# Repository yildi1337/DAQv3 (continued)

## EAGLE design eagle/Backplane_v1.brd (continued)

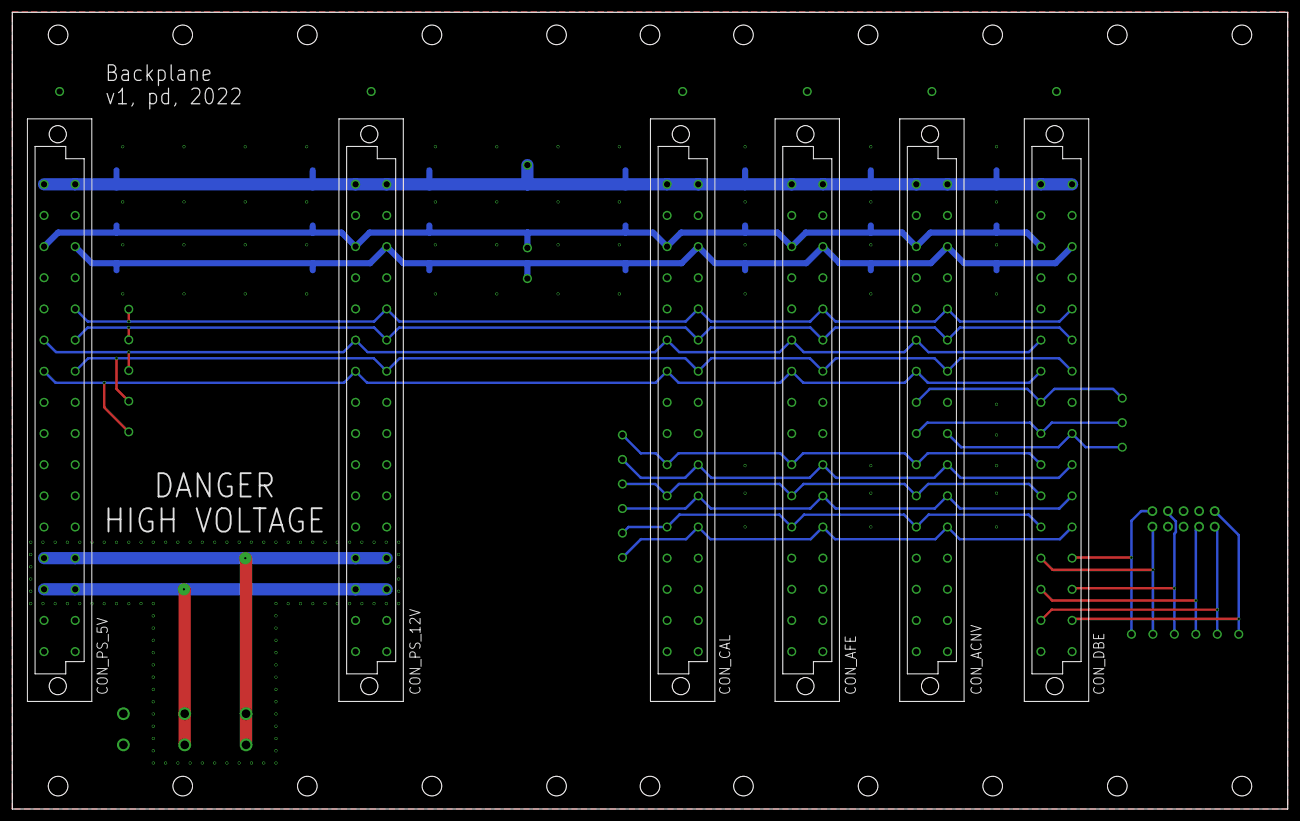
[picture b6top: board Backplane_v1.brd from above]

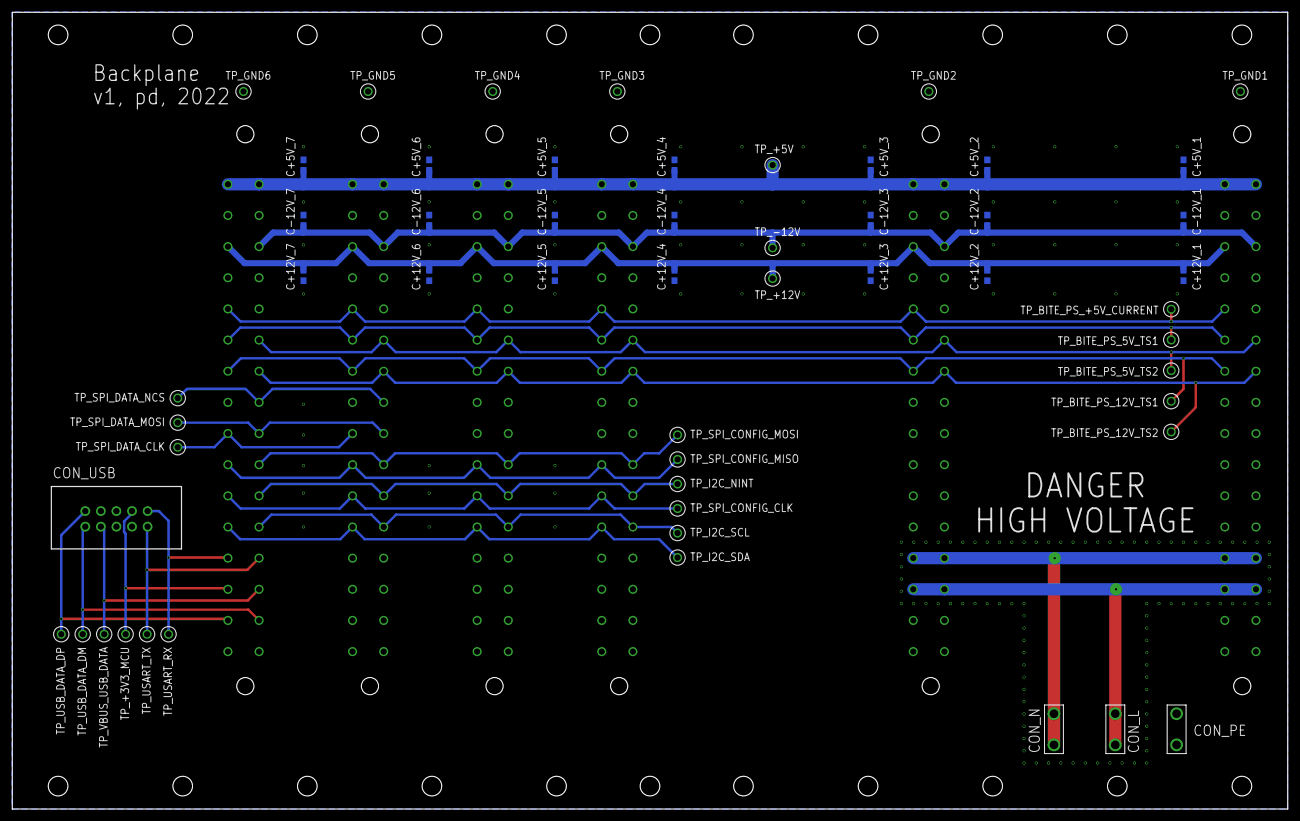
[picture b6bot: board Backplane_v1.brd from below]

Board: 2 copper layers, 208.0 x 129.9 mm, 60 parts (54 on the bottom side), 26 nets.

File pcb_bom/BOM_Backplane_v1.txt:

Stückliste exportiert aus D:/OneDrive/Elektronikprojekte/DAQ v3 STM32H7/Eagle/Backplane v1/Backplane_v1.sch am 20.03.2022 14:57

Qty Value          Device                          Package                         Parts                                                                                                                                                                                                                                                                                                                                                                                                                             Description                POPULARITY SPICEPREFIX
29                 RSPRO-1MM-TERMINAL-POST-2622034 RSPRO-1MM-TERMINAL-POST-2622034 TP_+3V3_MCU, TP_+5V, TP_+12V, TP_-12V, TP_BITE_PS_+5V_CURRENT, TP_BITE_PS_5V_TS1, TP_BITE_PS_5V_TS2, TP_BITE_PS_12V_TS1, TP_BITE_PS_12V_TS2, TP_GND1, TP_GND2, TP_GND3, TP_GND4, TP_GND5, TP_GND6, TP_I2C_NINT, TP_I2C_SCL, TP_I2C_SDA, TP_SPI_CONFIG_CLK, TP_SPI_CONFIG_MISO, TP_SPI_CONFIG_MOSI, TP_SPI_DATA_CLK, TP_SPI_DATA_MOSI, TP_SPI_DATA_NCS, TP_USART_RX, TP_USART_TX, TP_USB_DATA_DM, TP_USB_DATA_DP, TP_VBUS_USB_DATA                                                  
6   09032326825    09032326825                     09032326825                     CON_ACNV, CON_AFE, CON_CAL, CON_DBE, CON_PS_5V, CON_PS_12V                                                                                                                                                                                                                                                                                                                                                                                                                         
21  100n           C-EUC0603                       C0603                           C+5V_1, C+5V_2, C+5V_3, C+5V_4, C+5V_5, C+5V_6, C+5V_7, C+12V_1, C+12V_2, C+12V_3, C+12V_4, C+12V_5, C+12V_6, C+12V_7, C-12V_1, C-12V_2, C-12V_3, C-12V_4, C-12V_5, C-12V_6, C-12V_7                                                                                                                                                                                                                                              CAPACITOR, European symbol 73         C          
3   63824-1        63824-1                         63824-1                         CON_L, CON_N, CON_PE                                                                                                                                                                                                                                                                                                                                                                                                                                                               
1   TST-105-01-T-D TST-105-01-T-D                  TST-105-01-T-D                  CON_USB

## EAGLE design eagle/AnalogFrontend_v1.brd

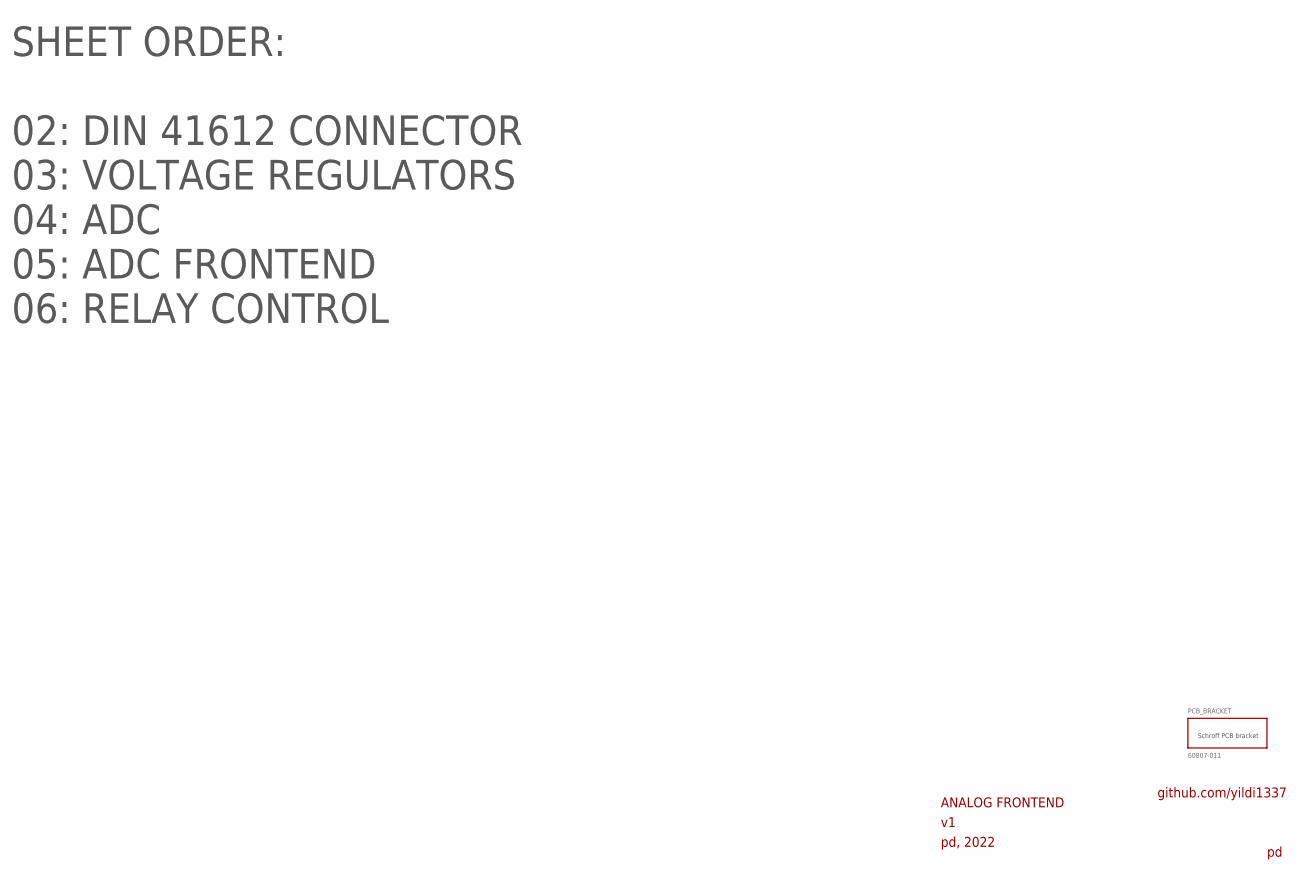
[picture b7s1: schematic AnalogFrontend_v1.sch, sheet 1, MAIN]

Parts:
PCB_BRACKET: 60807-011

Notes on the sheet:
ANALOG FRONTEND
pd, 2022
github.com/yildi1337
SHEET ORDER: 02: DIN 41612 CONNECTOR 03: VOLTAGE REGULATORS 04: ADC 05: ADC FRONTEND 06: RELAY CONTROL

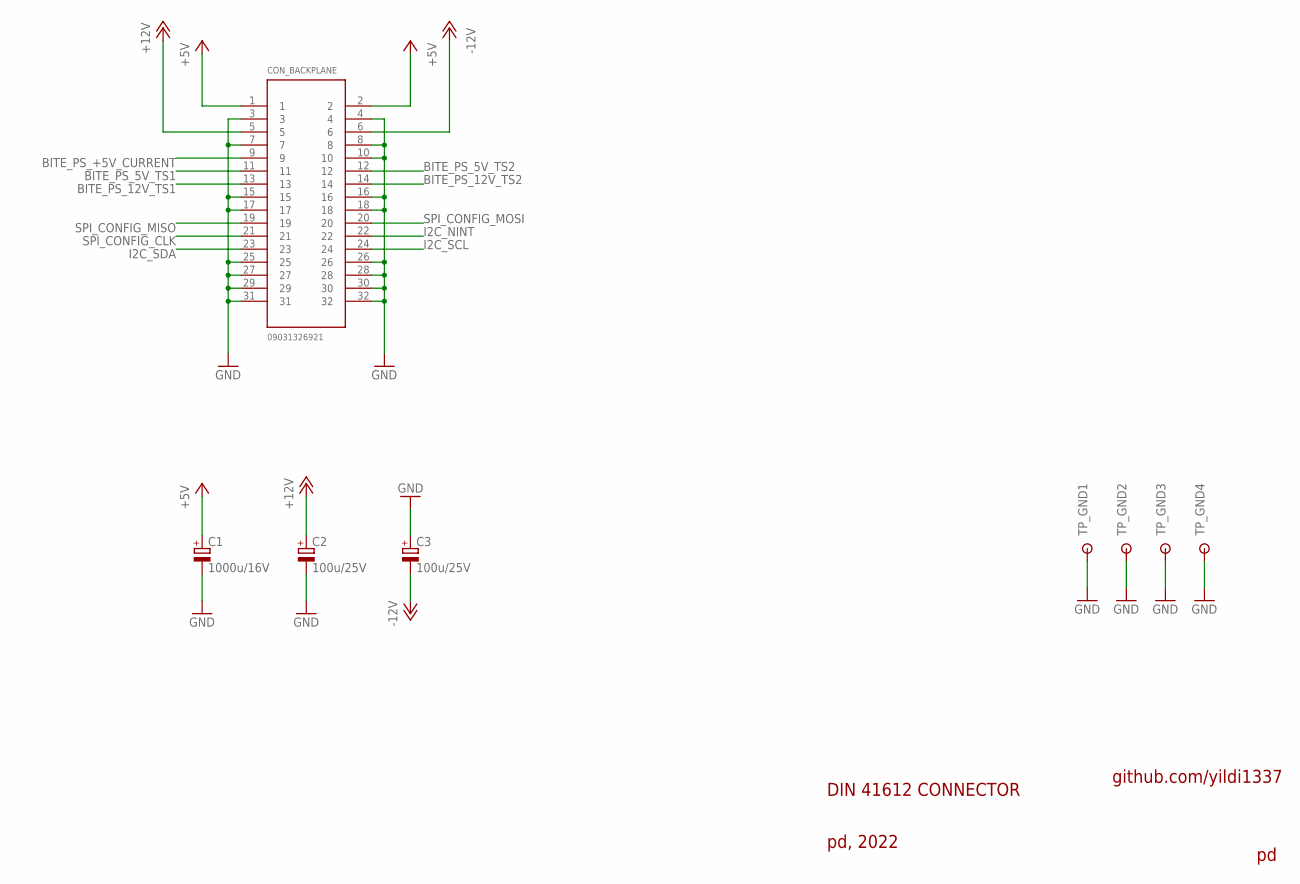
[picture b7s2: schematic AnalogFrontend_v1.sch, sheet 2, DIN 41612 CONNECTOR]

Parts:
C1: 1000u/16V; 153CLV-1010
C2, C3: 100u/25V; 153CLV-0810
CON_BACKPLANE: 09031326921
TP_GND1, TP_GND2, TP_GND3, TP_GND4: RSPRO-1MM-TERMINAL-POST-2622034

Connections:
+5V: C1.+, CON_BACKPLANE.1, CON_BACKPLANE.2; also elsewhere on the board
+12V: C2.+, CON_BACKPLANE.5; also elsewhere on the board
-12V: C3.-, CON_BACKPLANE.6; also elsewhere on the board
BITE_PS_5V_TS1: CON_BACKPLANE.11
BITE_PS_5V_TS2: CON_BACKPLANE.12
BITE_PS_12V_TS1: CON_BACKPLANE.13
BITE_PS_12V_TS2: CON_BACKPLANE.14
BITE_PS_+5V_CURRENT: CON_BACKPLANE.9
GND: C1.-, C2.-, C3.+, CON_BACKPLANE.3, CON_BACKPLANE.4, CON_BACKPLANE.7, CON_BACKPLANE.8, CON_BACKPLANE.10, CON_BACKPLANE.15, CON_BACKPLANE.16, CON_BACKPLANE.17, CON_BACKPLANE.18, CON_BACKPLANE.25, CON_BACKPLANE.26, CON_BACKPLANE.27, CON_BACKPLANE.28, CON_BACKPLANE.29, CON_BACKPLANE.30, CON_BACKPLANE.31, CON_BACKPLANE.32, TP_GND1.P$1, TP_GND2.P$1, TP_GND3.P$1, TP_GND4.P$1; also elsewhere on the board
I2C_NINT: CON_BACKPLANE.22; also elsewhere on the board
I2C_SCL: CON_BACKPLANE.24; also elsewhere on the board
I2C_SDA: CON_BACKPLANE.23; also elsewhere on the board
SPI_CONFIG_CLK: CON_BACKPLANE.21; also elsewhere on the board
SPI_CONFIG_MISO: CON_BACKPLANE.19; also elsewhere on the board
SPI_CONFIG_MOSI: CON_BACKPLANE.20; also elsewhere on the board

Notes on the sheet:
DIN 41612 CONNECTOR
pd, 2022
github.com/yildi1337

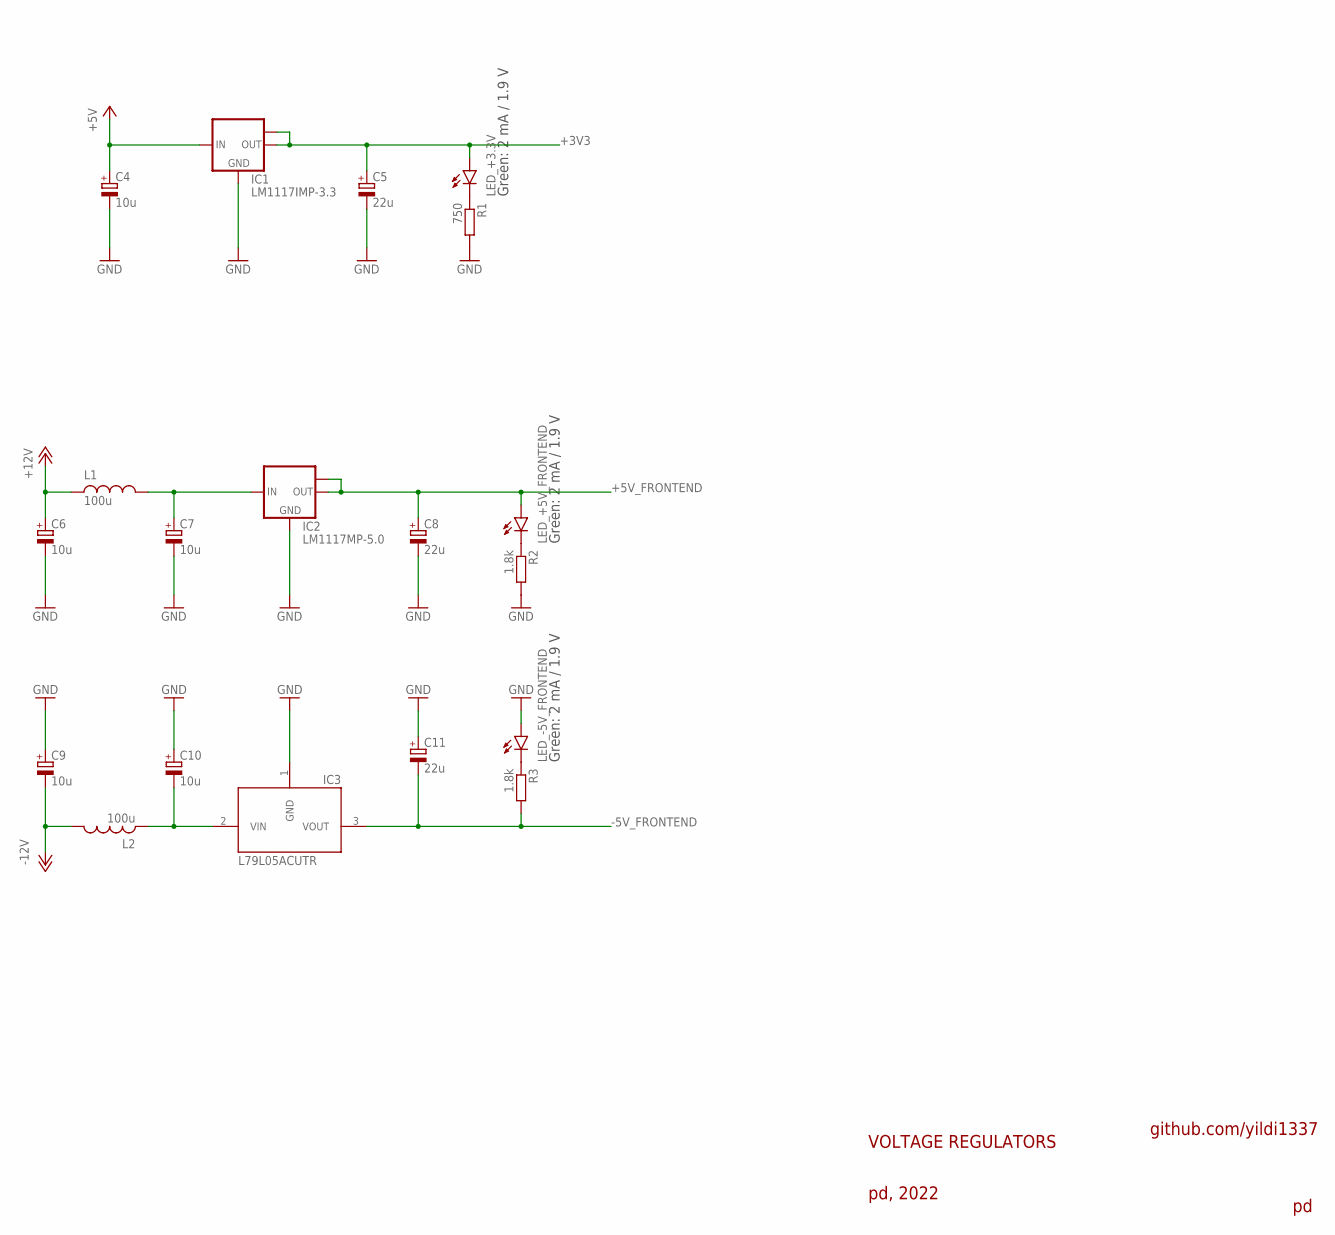
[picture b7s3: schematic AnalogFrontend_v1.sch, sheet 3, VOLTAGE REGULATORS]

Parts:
C4, C6, C7, C9, C10: 10u; CT3216
C5, C8, C11: 22u; CT6032
IC1: LM1117IMP-3.3; SOT223
IC2: LM1117MP-5.0; SOT223
IC3: L79L05ACUTR
L1, L2: 100u; VLS6045AF-101M
LED_+3.3V, LED_+5V_FRONTEND: LEDCHIP-LED0603; CHIP-LED0603
LED_-5V_FRONTEND: LEDCHIP-LED0603; CHIP-LED0603
R1: 750; R0603
R2, R3: 1.8k; R0603

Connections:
+3V3: C5.+, IC1.2 (OUT), IC1.TAB (OUT1), LED_+3.3V.A; also elsewhere on the board
+5V: C4.+, IC1.3 (IN); also elsewhere on the board
+5V_FRONTEND: C8.+, IC2.2 (OUT), IC2.TAB (OUT1), LED_+5V_FRONTEND.A; also elsewhere on the board
+12V: C6.+, L1.1; also elsewhere on the board
-5V_FRONTEND: C11.-, IC3.3 (VOUT), R3.2; also elsewhere on the board
-12V: C9.-, L2.2; also elsewhere on the board
GND: C4.-, C5.-, C6.-, C7.-, C8.-, C9.+, C10.+, C11.+, IC1.1 (GND), IC2.1 (GND), IC3.1 (GND), LED_-5V_FRONTEND.A, R1.2, R2.2; also elsewhere on the board
unnamed: LED_+5V_FRONTEND.C, R2.1
unnamed: C7.+, IC2.3 (IN), L1.2
unnamed: C10.-, IC3.2 (VIN), L2.1
unnamed: LED_-5V_FRONTEND.C, R3.1
unnamed: LED_+3.3V.C, R1.1

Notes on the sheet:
VOLTAGE REGULATORS
pd, 2022
github.com/yildi1337
Green: 2 mA / 1.9 V

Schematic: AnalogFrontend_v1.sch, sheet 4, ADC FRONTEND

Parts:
C57, C58, C634545, C644545: 100n; C0603
C61, C62: 1n; C0603
CON_INT_CH1, CON_INT_CH2: 2337019-1
CON_IN_CH1, CON_IN_CH2: DELOCK_65848
CON_OUT_CH1, CON_OUT_CH2: DELOCK_65848
IC9: OP27GSZ; SO08
LED_SHORT_CH1, LED_SHORT_CH2: 113-305-04
OP1, OP2: LT1028CS8
R33, R34: 1M; R0603
R3164654, R3245454: 150; R0603
RELAY1, RELAY2: 5-1462037-8
TP_FDA1_IN, TP_FDA2_IN: RSPRO-1MM-TERMINAL-POST-2622034

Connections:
+5V: C634545.1, C644545.1, RELAY1.6, RELAY2.6; also elsewhere on the board
+5V_FRONTEND: C57.2, IC9.7 (V+); also elsewhere on the board
-5V_FRONTEND: C58.1, IC9.4 (V-); also elsewhere on the board
GND: C57.1, C58.2, C61.2, C62.2, C634545.2, C644545.2, CON_INT_CH1.G1 (GND), CON_INT_CH1.G2 (GND), CON_INT_CH2.G1 (GND), CON_INT_CH2.G2 (GND), CON_IN_CH1.G1 (G), CON_IN_CH1.G2 (G), CON_IN_CH1.G3 (G), CON_IN_CH1.G4 (G), CON_IN_CH2.G1 (G), CON_IN_CH2.G2 (G), CON_IN_CH2.G3 (G), CON_IN_CH2.G4 (G), LED_SHORT_CH1.- (C), LED_SHORT_CH2.- (C), R33.1, R34.1, RELAY1.4, RELAY2.4; also elsewhere on the board
unnamed: C61.1, R33.2
unnamed: C62.1, R34.2
unnamed: CON_IN_CH1.S, RELAY1.2
unnamed: CON_IN_CH2.S, RELAY2.2
unnamed: LED_SHORT_CH1.+ (A), R3164654.2
unnamed: LED_SHORT_CH2.+ (A), R3245454.2
unnamed: R3245454.1, RELAY2.5
unnamed: R3164654.1, RELAY1.5
RD_OUT1: RELAY1.1; also elsewhere on the board
RD_OUT2: RELAY1.8; also elsewhere on the board
RD_OUT3: RELAY2.1; also elsewhere on the board
RD_OUT4: RELAY2.8; also elsewhere on the board
V+: OP1.7 (V+), OP2.7 (V+)
V-: OP1.4 (V-), OP2.4 (V-)

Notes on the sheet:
ADC FRONTEND
pd, 2022
n.c.

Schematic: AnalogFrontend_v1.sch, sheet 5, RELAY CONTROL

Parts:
C65: 1u; C0603
C66, C99: 100n; C0603
IC11: TCA9534ADWR
R27, R28, R29, R30: 100; R0603
RD: MAX4820EUP+
TP_I2C_NINT, TP_I2C_SCL, TP_I2C_SDA: RSPRO-1MM-TERMINAL-POST-2622034
TP_RD_NRESET: RSPRO-1MM-TERMINAL-POST-2622034
TP_RD_SPI_NCS: RSPRO-1MM-TERMINAL-POST-2622034

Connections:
+3V3: C65.1, C66.1, C99.1, IC11.16 (VCC), RD.1 (VCC), RD.2 (!SET), RD.15 (COM); also elsewhere on the board
+5V: R27.2, R28.2, R29.2, R30.2; also elsewhere on the board
GND: C65.2, C66.2, C99.2, IC11.1 (A0), IC11.2 (A1), IC11.3 (A2), IC11.8 (GND), RD.9 (GND), RD.12 (PGND), RD.18 (PGND), RD.21 (GND); also elsewhere on the board
I2C_NINT: IC11.13 (!INT), TP_I2C_NINT.P$1; also elsewhere on the board
I2C_SCL: IC11.14 (SCL), TP_I2C_SCL.P$1; also elsewhere on the board
I2C_SDA: IC11.15 (SDA), TP_I2C_SDA.P$1; also elsewhere on the board
RD_NRESET: IC11.7 (P3), RD.3 (!RESET), TP_RD_NRESET.P$1
RD_OUT1: R27.1, RD.20 (OUT1); also elsewhere on the board
RD_OUT2: R28.1, RD.19 (OUT2); also elsewhere on the board
RD_OUT3: R29.1, RD.17 (OUT3); also elsewhere on the board
RD_OUT4: R30.1, RD.16 (OUT4); also elsewhere on the board
RD_SPI_NCS: IC11.6 (P2), RD.4 (!CS), TP_RD_SPI_NCS.P$1
SPI_CONFIG_CLK: RD.6 (SCLK); also elsewhere on the board
SPI_CONFIG_MISO: RD.7 (DOUT); also elsewhere on the board
SPI_CONFIG_MOSI: RD.5 (DIN); also elsewhere on the board

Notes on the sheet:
RELAY CONTROL
pd, 2022
n.c.
I2C SLAVE ADDRESS: 0b0111000

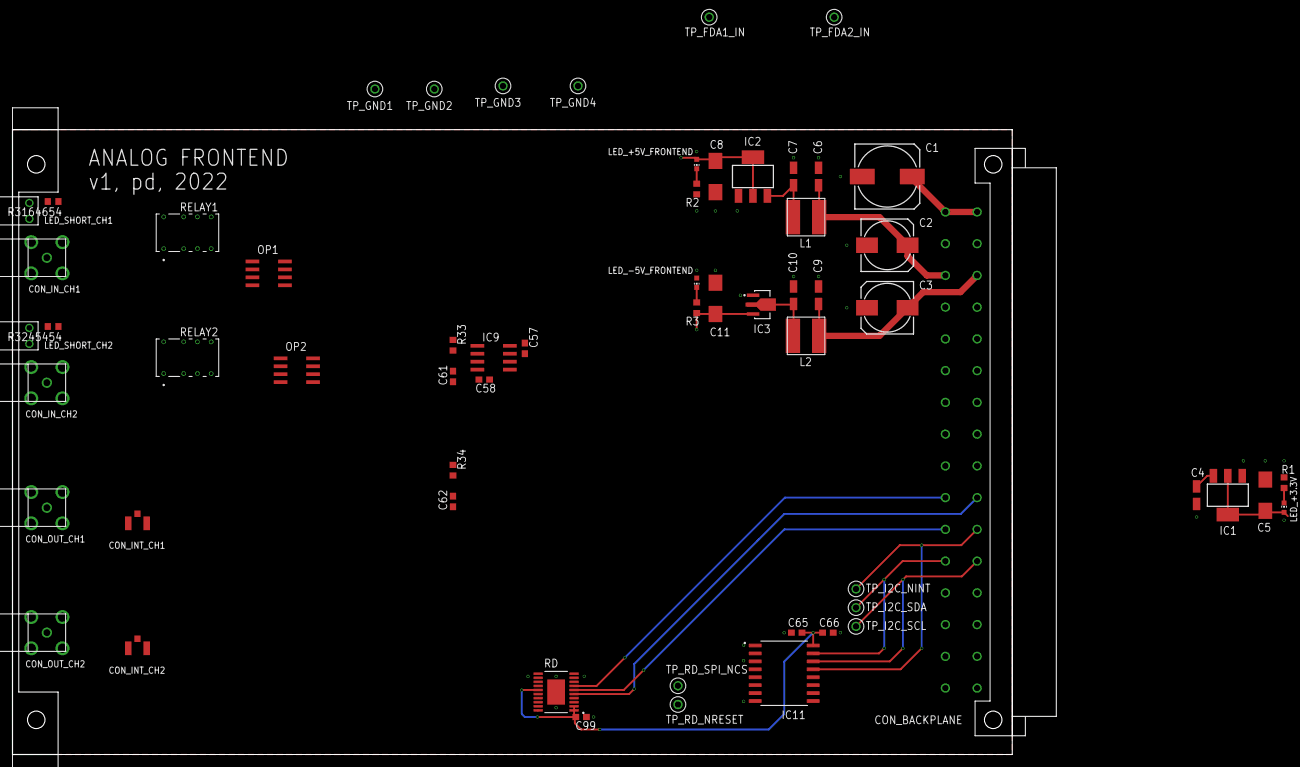
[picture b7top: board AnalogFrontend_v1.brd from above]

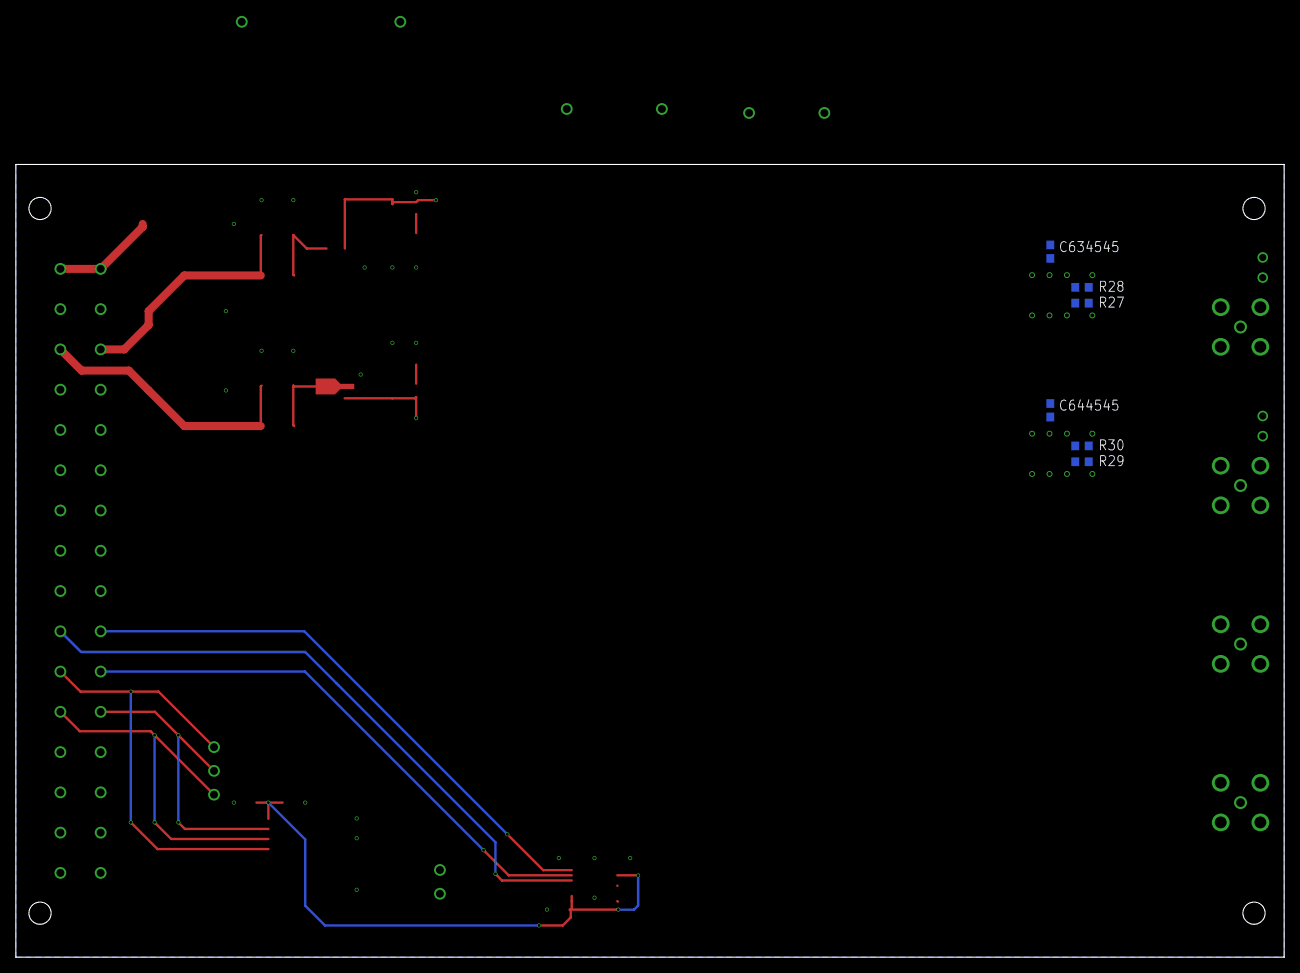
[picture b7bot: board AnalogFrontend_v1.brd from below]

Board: 2 copper layers, 160.0 x 100.0 mm, 67 parts (6 on the bottom side), 34 nets.

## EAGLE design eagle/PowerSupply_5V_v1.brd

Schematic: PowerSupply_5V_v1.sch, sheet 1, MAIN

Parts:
PCB_BRACKET: 60807-011

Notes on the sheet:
POWER SUPPLY +5 V
pd, 2022
github.com/yildi1337
SHEET ORDER: 02: DIN 41612 CONNECTOR 03: POWER SUPPLY +5 V

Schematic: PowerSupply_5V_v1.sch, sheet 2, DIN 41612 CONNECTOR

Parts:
CON_BACKPLANE: 09031326921
TP_GND1, TP_GND2, TP_GND3, TP_GND4: RSPRO-1MM-TERMINAL-POST-2622034
TS1, TS2: NB-PTCO-160

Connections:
+5V: CON_BACKPLANE.1, CON_BACKPLANE.2; also elsewhere on the board
+12V: CON_BACKPLANE.5
-12V: CON_BACKPLANE.6
BITE_PS_5V_TS1: CON_BACKPLANE.11, TS1.1
BITE_PS_5V_TS2: CON_BACKPLANE.12, TS2.1
BITE_PS_12V_TS1: CON_BACKPLANE.13
BITE_PS_12V_TS2: CON_BACKPLANE.14
BITE_PS_+5V_CURRENT: CON_BACKPLANE.9; also elsewhere on the board
GND: CON_BACKPLANE.3, CON_BACKPLANE.4, CON_BACKPLANE.7, CON_BACKPLANE.8, CON_BACKPLANE.10, CON_BACKPLANE.15, CON_BACKPLANE.16, CON_BACKPLANE.17, CON_BACKPLANE.18, CON_BACKPLANE.19, CON_BACKPLANE.20, CON_BACKPLANE.21, CON_BACKPLANE.22, CON_BACKPLANE.23, CON_BACKPLANE.24, CON_BACKPLANE.29, CON_BACKPLANE.30, CON_BACKPLANE.31, CON_BACKPLANE.32, TP_GND1.P$1, TP_GND2.P$1, TP_GND3.P$1, TP_GND4.P$1, TS1.2, TS2.2; also elsewhere on the board
L: CON_BACKPLANE.27, CON_BACKPLANE.28; also elsewhere on the board
N: CON_BACKPLANE.25, CON_BACKPLANE.26; also elsewhere on the board

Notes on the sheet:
DIN 41612 CONNECTOR
pd, 2022
github.com/yildi1337

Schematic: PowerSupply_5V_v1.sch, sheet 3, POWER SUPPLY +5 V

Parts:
BR1: GBJ610
C1, C2, C3, C4: 10n/1kV; C1808
C5, C6, C7, C8, C9, C10, C11, C12, C13: 15000u/16V; EEUHD1C153
C14: 10u/16V; 153CLV-0405
C15, C17, C18, C20, C21, C22: 100n; C0603
C16: 1000u/16V; 153CLV-1010
C19: 470n; C0603
FUSE_+5V: 0031.8201
HS1: FK 237 SA 220 O; FK_237_SA_220_O
IC1: MIC29300-5.0WT
IC2: ACS712ELCTR-05B-T
LED_+5V_OK: 113-314-04
OP1: MCP6L1T-E/OT
R1: 82/2W; R2010
R2: 150; R0603
R3: 0; R0603
R4: 3k; R0603
R5: 2k; R0603
R6, R7: 100k; R0603
R8: 27k; R0603
SWITCH_+5V: RSPRO-SPDT-SLIDE-SWITCH-7347334
TF1: FL 24/6; FL_24-6
TP_+5V: RSPRO-1MM-TERMINAL-POST-2622034
TP_BITE_PS_+5V_CURRENT: RSPRO-1MM-TERMINAL-POST-2622034
TP_HALL_SENSOR_VIOUT: RSPRO-1MM-TERMINAL-POST-2622034
TP_RECT_OUT: RSPRO-1MM-TERMINAL-POST-2622034
TP_TF_SEC_A: RSPRO-1MM-TERMINAL-POST-2622034
TP_TF_SEC_B: RSPRO-1MM-TERMINAL-POST-2622034

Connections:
+5V: C18.1, C22.1, FUSE_+5V.2, IC2.8 (VCC), OP1.2 (VDD), R2.2, R7.2; also elsewhere on the board
BITE_PS_+5V_CURRENT: C21.1, OP1.1 (VOUT), R8.2, TP_BITE_PS_+5V_CURRENT.P$1; also elsewhere on the board
GND: BR1.-, C1.2, C3.1, C5.-, C6.-, C7.-, C8.-, C9.-, C10.-, C11.-, C12.-, C13.-, C14.-, C15.2, C16.-, C17.2, C18.2, C19.2, C20.2, C21.2, C22.2, IC1.2 (GND), IC2.5 (GND), LED_+5V_OK.- (C), OP1.5 (VSS), R1.1, R6.1; also elsewhere on the board
L: TF1.P1A; also elsewhere on the board
N: TF1.P2B; also elsewhere on the board
unnamed: C19.1, IC2.6 (FILTER)
unnamed: FUSE_+5V.1, IC2.3 (IP-), IC2.4 (IP-), R3.2
unnamed: BR1.+, C2.2, C4.1, C5.+, C6.+, C7.+, C8.+, C9.+, C10.+, C11.+, C12.+, C13.+, R1.2, SWITCH_+5V.3 (NO), TP_RECT_OUT.P$1
unnamed: IC2.7 (VIOUT), R4.1, TP_HALL_SENSOR_VIOUT.P$1
unnamed: TF1.P1B, TF1.P2A
unnamed: BR1.L, C1.1, C2.1, TF1.S1A, TF1.S2A, TP_TF_SEC_A.P$1
unnamed: LED_+5V_OK.+ (A), R2.1
unnamed: C16.+, C17.1, IC1.3 (OUT), IC2.1 (IP+), IC2.2 (IP+), R3.1, TP_+5V.P$1
unnamed: R4.2, R5.1
unnamed: BR1.N, C3.2, C4.2, TF1.S1B, TF1.S2B, TP_TF_SEC_B.P$1
unnamed: C20.1, OP1.3 (VIN+), R6.2, R7.1
unnamed: C14.+, C15.1, IC1.1 (IN), SWITCH_+5V.2 (COM)
unnamed: OP1.4 (VIN-), R5.2, R8.1

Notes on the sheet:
POWER SUPPLY +5 V
pd, 2022
github.com/yildi1337
9 x EEUHD1C153
4 x 1808AC103KAT2A
n.c.
2.5 V +/- 185 mV/A
2.5 V -/+ 1000 mV/A
Gain: 5.4

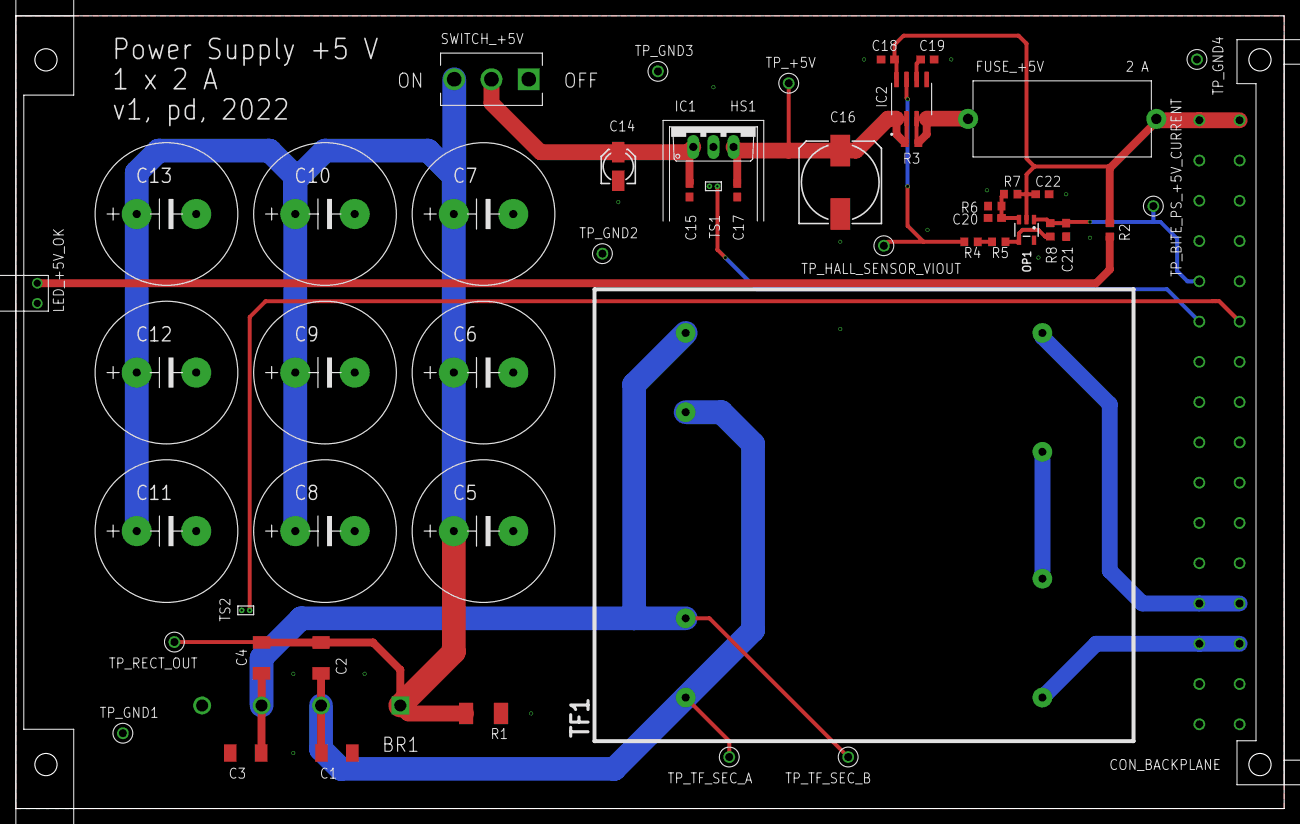
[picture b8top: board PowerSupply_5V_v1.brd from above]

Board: 2 copper layers, 160.0 x 100.0 mm, 53 parts (0 on the bottom side), 20 nets.

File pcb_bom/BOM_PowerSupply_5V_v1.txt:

Stückliste exportiert aus D:/OneDrive/Elektronikprojekte/DAQ v3 STM32H7/Eagle/Power Supply 5V v1/PowerSupply_5V_v1.sch am 20.03.2022 15:07

Qty Value                           Device                          Package                         Parts                                                                                                                           Description                          POPULARITY SPICEPREFIX
10                                  RSPRO-1MM-TERMINAL-POST-2622034 RSPRO-1MM-TERMINAL-POST-2622034 TP_+5V, TP_BITE_PS_+5V_CURRENT, TP_GND1, TP_GND2, TP_GND3, TP_GND4, TP_HALL_SENSOR_VIOUT, TP_RECT_OUT, TP_TF_SEC_A, TP_TF_SEC_B                                                            
1   0                               R-EU_R0603                      R0603                           R3                                                                                                                              RESISTOR, European symbol            70         R          
1   0031.8201                       0031.8201                       0031.8201                       FUSE_+5V                                                                                                                                                                                   
1   09031326921                     09031326921                     09031326921                     CON_BACKPLANE                                                                                                                                                                              
1   1000u/16V                       CPOL-EU153CLV-1010              153CLV-1010                     C16                                                                                                                             POLARIZED CAPACITOR, European symbol 0          C          
2   100k                            R-EU_R0603                      R0603                           R6, R7                                                                                                                          RESISTOR, European symbol            70         R          
6   100n                            C-EUC0603                       C0603                           C15, C17, C18, C20, C21, C22                                                                                                    CAPACITOR, European symbol           73         C          
4   10n/1kV                         C-EUC1808                       C1808                           C1, C2, C3, C4                                                                                                                  CAPACITOR, European symbol           0          C          
1   10u/16V                         CPOL-EU153CLV-0405              153CLV-0405                     C14                                                                                                                             POLARIZED CAPACITOR, European symbol 0          C          
1   113-314-04                      113-314-04                      113-314-04                      LED_+5V_OK                                                                                                                                                                                 
1   150                             R-EU_R0603                      R0603                           R2                                                                                                                              RESISTOR, European symbol            70         R          
9   15000u/16V                      EEUHD1C153                      EEUHD1C153                      C5, C6, C7, C8, C9, C10, C11, C12, C13                                                                                                                                                     
1   27k                             R-EU_R0603                      R0603                           R8                                                                                                                              RESISTOR, European symbol            70         R          
1   2k                              R-EU_R0603                      R0603                           R5                                                                                                                              RESISTOR, European symbol            70         R          
1   3k                              R-EU_R0603                      R0603                           R4                                                                                                                              RESISTOR, European symbol            70         R          
1   470n                            C-EUC0603                       C0603                           C19                                                                                                                             CAPACITOR, European symbol           73         C          
1   60807-011                       60807-011                       60807-011                       PCB_BRACKET                                                                                                                                                                                
1   82/2W                           R-EU_R2010                      R2010                           R1                                                                                                                              RESISTOR, European symbol            3          R          
1   ACS712ELCTR-05B-T               ACS712ELCTR-05B-T               ACS712ELCTR-05B-T               IC2                                                                                                                                                                                        
1   FK 237 SA 220 O                 FK_237_SA_220_O                 FK_237_SA_220_O                 HS1                                                                                                                                                                                        
1   FL 24/6                         FL_24-6                         FL_24-6                         TF1                                                                                                                                                                                        
1   GBJ610                          GBJ610                          GBJ610                          BR1                                                                                                                                                                                        
1   MCP6L1T-E/OT                    MCP6L1T-E/OT                    MCP6L1T-E/OT                    OP1                                                                                                                                                                                        
1   MIC29300-5.0WT                  MIC29300-5.0WT                  MIC29300-5.0WT                  IC1                                                                                                                                                                                        
2   NB-PTCO-160                     NB-PTCO-160                     NB-PTCO-160                     TS1, TS2                                                                                                                                                                                   
1   RSPRO-SPDT-SLIDE-SWITCH-7347334 RSPRO-SPDT-SLIDE-SWITCH-7347334 RSPRO-SPDT-SLIDE-SWITCH-7347334 SWITCH_+5V

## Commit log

2022-07-30 Added pictures of modules
2022-07-30 Added step files of modules
2022-07-30 Added bom files
2022-07-30 Added gerber files
2022-07-30 Added pictures of the bare boards
2022-07-30 Added schematics
2022-07-30 Added EAGLE project files
2022-07-30 Updated bom files
2022-07-30 Updated gerber files
2022-07-30 Added complete CAD model
2022-07-31 Added missing pages
2022-08-11 Minor changes to 3D model
2022-09-24 Added firmware
2022-09-24 Added labview sources (data receiver)
2022-09-24 Added USB driver
2022-09-24 Added some noise measurements
2022-09-25 Added debug and control interface
2022-09-25 Added labview source code of signal analyzer
2022-09-25 Updated noise measurements
2022-09-25 Updated noise measurement results
2022-09-25 Added noise measurement results
2022-09-25 Updated measurement results
2022-09-26 Updated readme and noise plots
